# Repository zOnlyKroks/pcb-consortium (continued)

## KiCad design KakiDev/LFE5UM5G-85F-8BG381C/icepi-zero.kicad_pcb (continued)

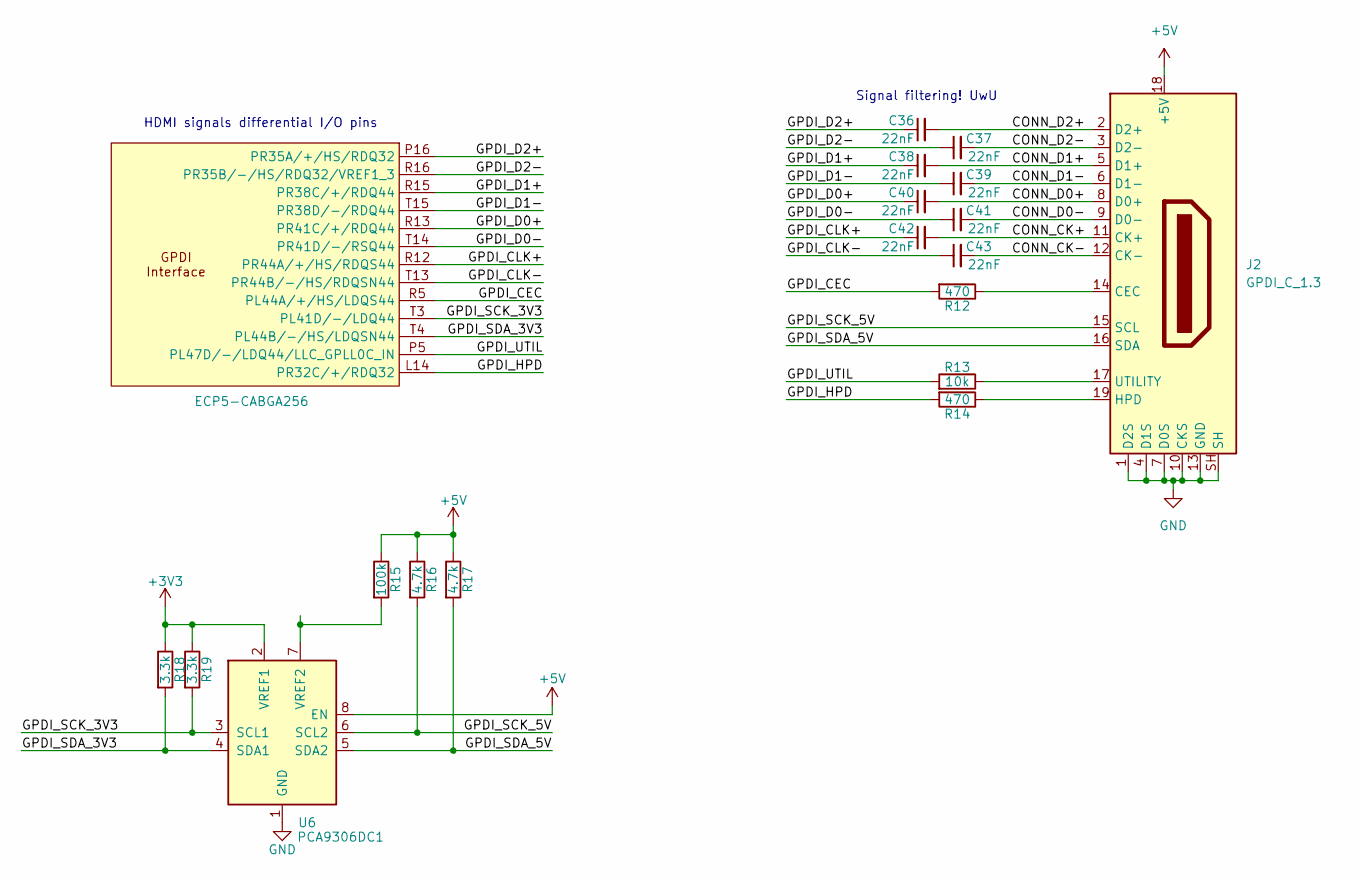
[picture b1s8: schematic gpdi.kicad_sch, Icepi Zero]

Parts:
C36, C37, C38, C39, C40, C41, C42, C43: 22nF; C_0603_1608Metric; Manufactuer Part Number 0402B223K500NT; LCSC Part # C1532
J2: GPDI_C_1.3; XKB Connection A71-05H4-111N1; Manufactuer Part Number A71-05H4-111N1; LCSC Part # C2682170
R12, R14: 470; R_0603_1608Metric; Manufactuer Part Number 0402WGF4700TCE; LCSC Part # C25117
R13: 10k; R_0603_1608Metric; Manufactuer Part Number 0402WGF1002TCE; LCSC Part # C25744
R15: 100k; R_0603_1608Metric; Manufactuer Part Number 0402WGF1003TCE; LCSC Part # C25741
R16, R17: 4.7k; R_0603_1608Metric; Manufactuer Part Number 0402WGF4701TCE; LCSC Part # C25900
R18, R19: 3.3k; R_0603_1608Metric; Manufactuer Part Number 0402WGF3301TCE; LCSC Part # C25890
U1: ECP5-CABGA256; BGA-256_14.0x14.0mm_Layout16x16_P0.8mm_Ball0.45mm_Pad0.32mm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; Manufactuer Part Number LFE5U-25F-6BG256C; LCSC Part # C1521614
U6: PCA9306DC1; VSSOP-8_2.3x2mm_P0.5mm; Manufactuer Part Number PCA9306DC1; LCSC Part # C129510

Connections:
+3V3: R18.1, R19.1, U6.2 (VREF1); also elsewhere on the board
+5V: J2.18 (+5V), R15.1, R16.1, R17.1, U6.8 (EN); also elsewhere on the board
/GPDI/CONN_CK+: C42.2, J2.11 (CK+)
/GPDI/CONN_CK-: C43.2, J2.12 (CK-)
/GPDI/CONN_D0+: C40.2, J2.8 (D0+)
/GPDI/CONN_D0-: C41.2, J2.9 (D0-)
/GPDI/CONN_D1+: C38.2, J2.5 (D1+)
/GPDI/CONN_D1-: C39.2, J2.6 (D1-)
/GPDI/CONN_D2+: C36.2, J2.2 (D2+)
/GPDI/CONN_D2-: C37.2, J2.3 (D2-)
/GPDI/GPDI_CEC: R12.2, U1.R5 (PL44A/+/HS/LDQS44)
/GPDI/GPDI_CLK+: C42.1, U1.R12 (PR44A/+/HS/RDQS44)
/GPDI/GPDI_CLK-: C43.1, U1.T13 (PR44B/-/HS/RDQSN44)
/GPDI/GPDI_D0+: C40.1, U1.R13 (PR41C/+/RDQ44)
/GPDI/GPDI_D0-: C41.1, U1.T14 (PR41D/-/RSQ44)
/GPDI/GPDI_D1+: C38.1, U1.R15 (PR38C/+/RDQ44)
/GPDI/GPDI_D1-: C39.1, U1.T15 (PR38D/-/RDQ44)
/GPDI/GPDI_D2+: C36.1, U1.P16 (PR35A/+/HS/RDQ32)
/GPDI/GPDI_D2-: C37.1, U1.R16 (PR35B/-/HS/RDQ32/VREF1_3)
/GPDI/GPDI_HPD: R14.2, U1.L14 (PR32C/+/RDQ32)
/GPDI/GPDI_SCK_3V3: R19.2, U1.T3 (PL41D/-/LDQ44), U6.3 (SCL1)
/GPDI/GPDI_SCK_5V: J2.15 (SCL), R16.2, U6.6 (SCL2)
/GPDI/GPDI_SDA_3V3: R18.2, U1.T4 (PL44B/-/HS/LDQSN44), U6.4 (SDA1)
/GPDI/GPDI_SDA_5V: J2.16 (SDA), R17.2, U6.5 (SDA2)
/GPDI/GPDI_UTIL: R13.2, U1.P5 (PL47D/-/LDQ44/LLC_GPLL0C_IN)
GND: J2.1 (D2S), J2.4 (D1S), J2.7 (D0S), J2.10 (CKS), J2.13 (GND), J2.SH, U6.1 (GND); also elsewhere on the board
unnamed: J2.14 (CEC), R12.1
unnamed: J2.19 (HPD), R14.1
unnamed: J2.17 (UTILITY), R13.1
unnamed: R15.2, U6.7 (VREF2)

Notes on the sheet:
HDMI signals differential I/O pins
Signal filtering! UwU

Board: 4 copper layers, 134 parts (0 on the bottom side), 246 nets, no tracks yet.

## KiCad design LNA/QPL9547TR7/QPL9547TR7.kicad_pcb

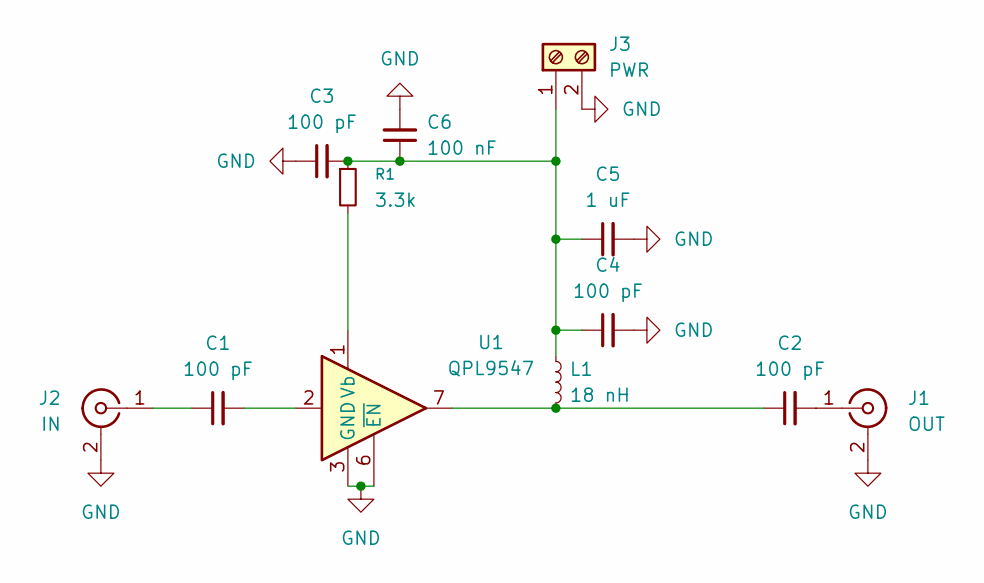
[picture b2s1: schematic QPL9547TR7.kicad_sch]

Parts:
C1, C2, C3, C4: 100 pF; C_0603_1608Metric
C5: 1 uF; C_0603_1608Metric
C6: 100 nF; C_0603_1608Metric
J1: OUT; SMA_BAT_Wireless_BWSMA-KWE-Z001
J2: IN; SMA_BAT_Wireless_BWSMA-KWE-Z001
J3: PWR; WJ500V-5.08-2P
L1: 18 nH; L_0805_2012Metric
R1: 3.3k; R_0603_1608Metric
U1: QPL9547; DFN-8-1EP_2x2mm_P0.5mm_EP0.8x1.6mm

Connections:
GND: C3.1, C4.2, C5.2, C6.2, J1.2 (Ext), J2.2 (Ext), J3.2, U1.3 (GND), U1.4 (GND), U1.5 (GND), U1.6 (~EN), U1.8 (GND), U1.9 (GND)
unnamed: C1.2, U1.2
unnamed: C2.1, L1.2, U1.7
unnamed: C2.2, J1.1 (In)
unnamed: C1.1, J2.1 (In)
unnamed: C3.2, C4.1, C5.1, C6.1, J3.1, L1.1, R1.1
unnamed: R1.2, U1.1 (Vb)

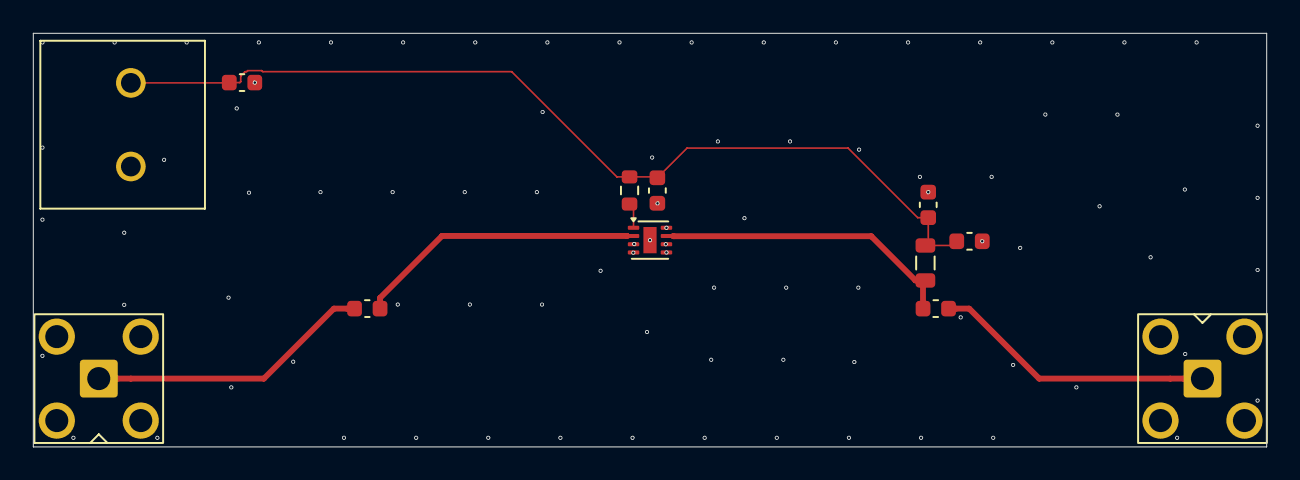
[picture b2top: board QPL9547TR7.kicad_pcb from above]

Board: 4 copper layers, 74.9 x 25.1 mm, 12 parts (0 on the bottom side), 7 nets.

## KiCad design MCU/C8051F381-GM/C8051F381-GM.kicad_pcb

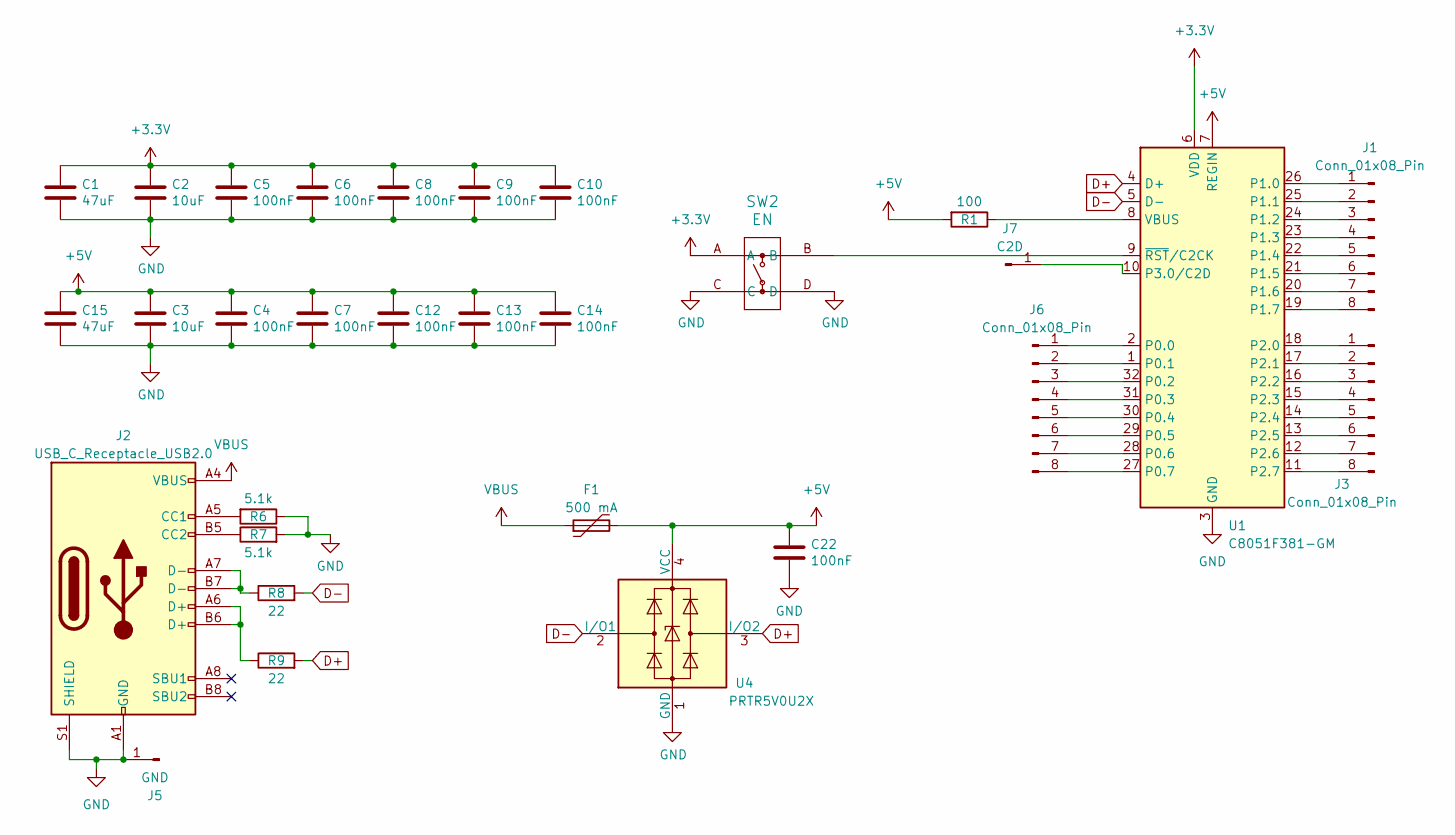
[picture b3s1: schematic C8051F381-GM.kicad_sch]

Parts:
C1, C15: 47uF; C_1206_3216Metric; LCSC C96123
C2, C3: 10uF; C_0603_1608Metric; LCSC C19702
C4, C5, C6, C7, C8, C9, C10, C12, C13, C14, C22: 100nF; C_0603_1608Metric; LCSC C14663
F1: 500 mA; Fuse_1206_3216Metric; LCSC C135341
J1, J3, J6: Conn_01x08_Pin; PinHeader_1x08_P2.54mm_Vertical
J2: USB_C_Receptacle_USB2.0; USB_C_Receptacle_HRO_TYPE-C-31-M-12; JlcRotOffset 180
J5: GND; PinHeader_1x01_P2.54mm_Vertical; LCSC Part # C492400
J7: C2D; PinHeader_1x01_P2.54mm_Vertical
R1: 100; R_0603_1608Metric; LCSC Part # C23186
R6, R7: 5.1k; R_0603_1608Metric; LCSC Part # C23186
R8, R9: 22; R_0603_1608Metric; LCSC Part # C23345
SW2: EN; KH-6X6X5H-STM_SKE; LCSC Part # C2837531
U1: C8051F381-GM; QFN-32-1EP_5x5mm_P0.5mm_EP3.3x3.3mm; LCSC Part # C1522096
U4: PRTR5V0U2X; SOT-143; LCSC C2827688

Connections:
+3.3V: C1.1, C2.1, C5.1, C6.1, C8.1, C9.1, C10.1, SW2.A, U1.6 (VDD)
+5V: C3.1, C4.1, C7.1, C12.1, C13.1, C14.1, C15.1, C22.1, F1.2, R1.2, U1.7 (REGIN), U4.4 (VCC)
D+: R9.2, U1.4 (D+), U4.3 (I/O2)
D-: R8.2, U1.5 (D-), U4.2 (I/O1)
GND: C1.2, C2.2, C3.2, C4.2, C5.2, C6.2, C7.2, C8.2, C9.2, C10.2, C12.2, C13.2, C14.2, C15.2, C22.2, J2.A1 (GND), J2.A12 (GND), J2.B1 (GND), J2.B12 (GND), J2.S1 (SHIELD), J5.1, R6.1, R7.2, SW2.C, SW2.D, U1.3 (GND), U1.33 (GND), U4.1 (GND)
unnamed: J1.1, U1.26 (P1.0)
unnamed: J1.2, U1.25 (P1.1)
unnamed: J1.3, U1.24 (P1.2)
unnamed: J1.4, U1.23 (P1.3)
unnamed: J1.5, U1.22 (P1.4)
unnamed: J1.6, U1.21 (P1.5)
unnamed: J1.7, U1.20 (P1.6)
unnamed: J1.8, U1.19 (P1.7)
unnamed: J2.A5 (CC1), R6.2
unnamed: J2.B5 (CC2), R7.1
unnamed: J2.A6 (D+), J2.B6 (D+), R9.1
unnamed: J2.A7 (D-), J2.B7 (D-), R8.1
unnamed: J3.1, U1.18 (P2.0)
unnamed: J3.2, U1.17 (P2.1)
unnamed: J3.3, U1.16 (P2.2)
unnamed: J3.4, U1.15 (P2.3)
unnamed: J3.5, U1.14 (P2.4)
unnamed: J3.6, U1.13 (P2.5)
unnamed: J3.7, U1.12 (P2.6)
unnamed: J3.8, U1.11 (P2.7)
unnamed: J6.1, U1.2 (P0.0)
unnamed: J6.2, U1.1 (P0.1)
unnamed: J6.3, U1.32 (P0.2)
unnamed: J6.4, U1.31 (P0.3)
unnamed: J6.5, U1.30 (P0.4)
unnamed: J6.6, U1.29 (P0.5)
unnamed: J6.7, U1.28 (P0.6)
unnamed: J6.8, U1.27 (P0.7)
unnamed: J7.1, U1.10 (P3.0/C2D)
unnamed: R1.1, U1.8 (VBUS)
unnamed: SW2.B, U1.9 (~RST/C2CK)
VBUS: F1.1, J2.A4 (VBUS), J2.A9 (VBUS), J2.B4 (VBUS), J2.B9 (VBUS)

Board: 2 copper layers, 30 parts (0 on the bottom side), 37 nets, no tracks yet.

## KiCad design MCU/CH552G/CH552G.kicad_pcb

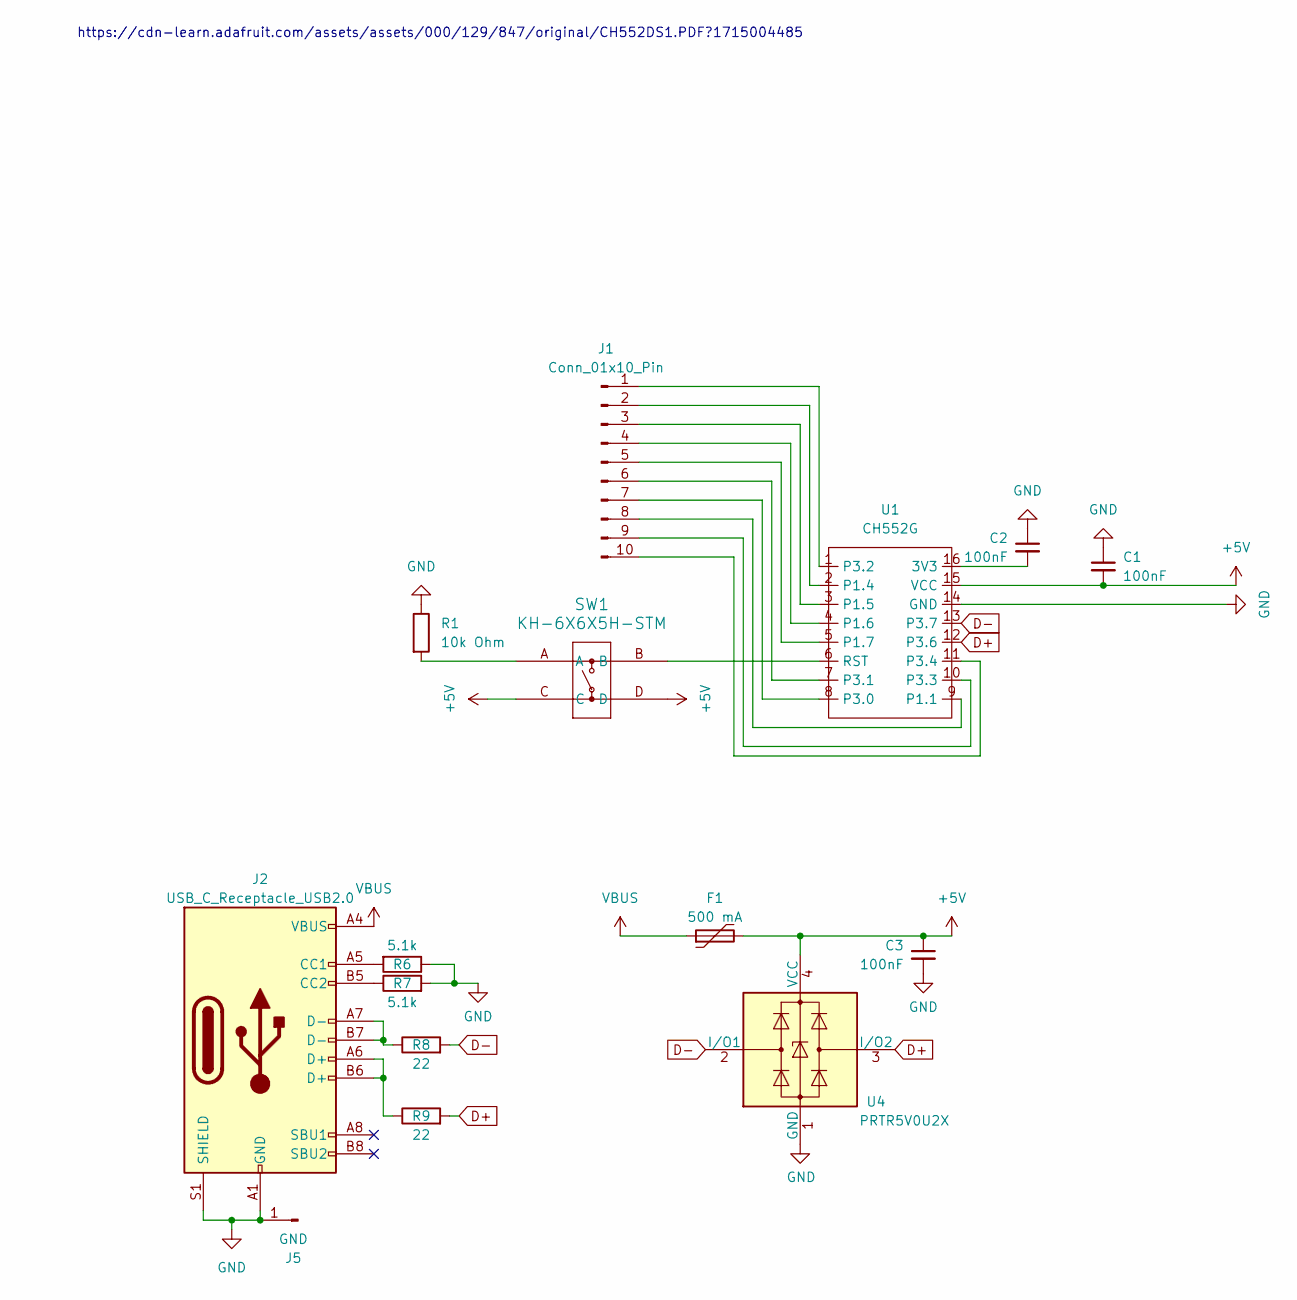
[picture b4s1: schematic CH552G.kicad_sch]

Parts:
C1, C2, C3: 100nF; C_0805_2012Metric; LCSC Part # C49678
F1: 500 mA; Fuse_1206_3216Metric; LCSC C135341
J1: Conn_01x10_Pin; PinHeader_1x10_P2.54mm_Vertical; LCSC Part # C492409
J2: USB_C_Receptacle_USB2.0; USB_C_Receptacle_HRO_TYPE-C-31-M-12; JlcRotOffset 180
J5: GND; PinHeader_1x01_P2.54mm_Vertical; LCSC Part # C492400
R1: 10k Ohm; R_0805_2012Metric; LCSC Part # C17414
R6, R7: 5.1k; R_0603_1608Metric; LCSC Part # C23186
R8, R9: 22; R_0603_1608Metric; LCSC Part # C23345
SW1: KH-6X6X5H-STM; KH-6X6X5H-STM_SKE; LCSC Part # C2837531
U1: CH552G; LCSC Part # C111292
U4: PRTR5V0U2X; SOT-143; LCSC C2827688

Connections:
+5V: C1.2, C3.1, F1.2, SW1.C, SW1.D, U1.15 (VCC), U4.4 (VCC)
D+: R9.2, U1.12 (P3.6), U4.3 (I/O2)
D-: R8.2, U1.13 (P3.7), U4.2 (I/O1)
GND: C1.1, C2.1, C3.2, J2.A1 (GND), J2.A12 (GND), J2.B1 (GND), J2.B12 (GND), J2.S1 (SHIELD), J5.1, R1.1, R6.1, R7.2, U1.14 (GND), U4.1 (GND)
unnamed: J1.1, U1.1 (P3.2)
unnamed: J1.2, U1.2 (P1.4)
unnamed: J1.3, U1.3 (P1.5)
unnamed: J1.4, U1.4 (P1.6)
unnamed: J1.5, U1.5 (P1.7)
unnamed: J1.6, U1.7 (P3.1)
unnamed: J1.7, U1.8 (P3.0)
unnamed: J1.8, U1.9 (P1.1)
unnamed: J1.9, U1.10 (P3.3)
unnamed: J1.10, U1.11 (P3.4)
unnamed: J2.A5 (CC1), R6.2
unnamed: J2.B5 (CC2), R7.1
unnamed: J2.A6 (D+), J2.B6 (D+), R9.1
unnamed: J2.A7 (D-), J2.B7 (D-), R8.1
unnamed: R1.2, SW1.A
unnamed: C2.2, U1.16 (3V3)
unnamed: SW1.B, U1.6 (RST)
VBUS: F1.1, J2.A4 (VBUS), J2.A9 (VBUS), J2.B4 (VBUS), J2.B9 (VBUS)

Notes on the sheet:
https://cdn-learn.adafruit.com/assets/assets/000/129/847/original/CH552DS1.PDF?1715004485

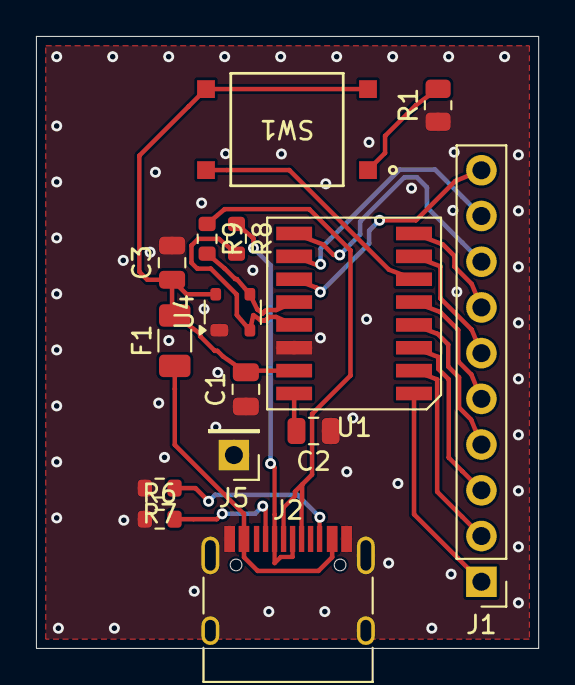
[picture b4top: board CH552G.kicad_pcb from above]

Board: 2 copper layers, 27.9 x 34.0 mm, 15 parts (0 on the bottom side), 22 nets.

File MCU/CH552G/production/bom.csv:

Designator,Footprint,Quantity,Value,LCSC Part #
"C1, C2, C3",0805,3,100nF,C49678
F1,1206,1,500 mA,C135341
J1,PinHeader_1x10_P2.54mm_Vertical,1,Conn_01x10_Pin,C492409
J2,USB_C_Receptacle_HRO_TYPE-C-31-M-12,1,USB_C_Receptacle_USB2.0,C165948
J5,PinHeader_1x01_P2.54mm_Vertical,1,GND,C492400
R1,0805,1,10k Ohm,C17414
"R6, R7",0603,2,5.1k,C23186
"R8, R9",0603,2,22,C23345
SW1,KH-6X6X5H-STM_SKE,1,KH-6X6X5H-STM,C2837531
U1,CH552G,1,CH552G,C111292
U4,SOT-143,1,PRTR5V0U2X,C2827688

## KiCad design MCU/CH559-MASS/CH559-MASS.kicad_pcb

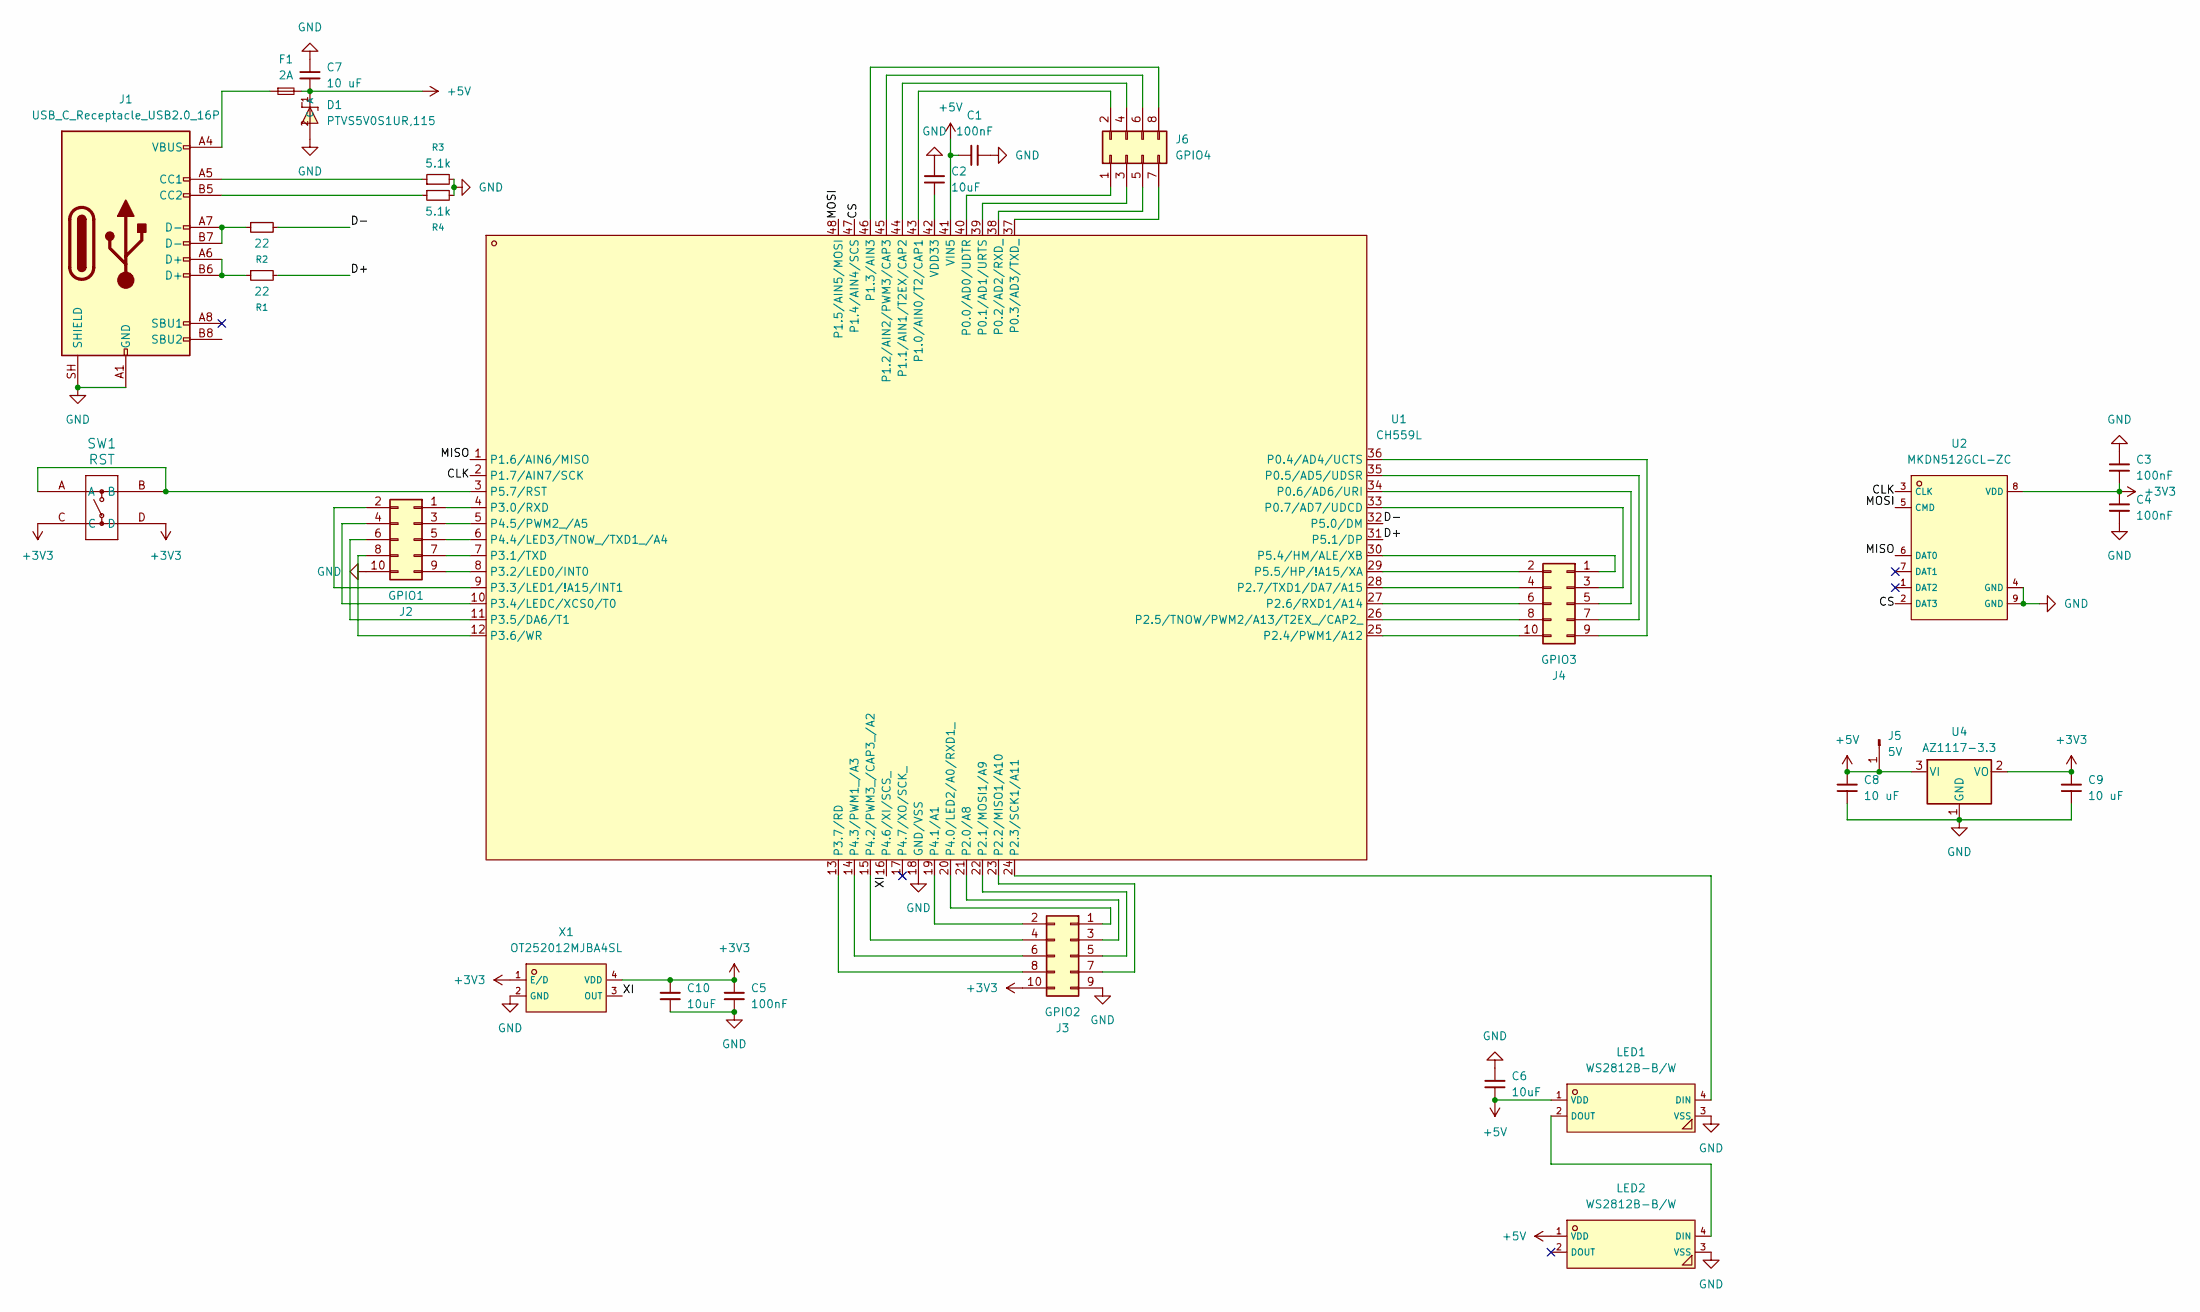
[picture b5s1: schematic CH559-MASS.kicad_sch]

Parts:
C1, C3, C4, C5: 100nF; C_0603_1608Metric
C2, C6: 10uF; C_0603_1608Metric
C7, C8, C9: 10 uF; C_0805_2012Metric
C10: 10uF; C_0805_2012Metric
D1: PTVS5V0S1UR,115; C478011_SOD-123_L2_8-W1_8-LS3_7-RD; LCSC C478011
F1: 2A; Fuse_0805_2012Metric
J1: USB_C_Receptacle_USB2.0_16P; USB_C_Receptacle_HRO_TYPE-C-31-M-12
J2: GPIO1; PinHeader_2x05_P2.54mm_Vertical
J3: GPIO2; PinHeader_2x05_P2.54mm_Vertical
J4: GPIO3; PinHeader_2x05_P2.54mm_Vertical
J5: 5V; PinHeader_1x01_P2.54mm_Vertical
J6: GPIO4; PinHeader_2x04_P2.54mm_Vertical
LED1, LED2: WS2812B-B/W; C2761795_LED-SMD_4P-L5_0-W5_0-TL_WS2812B-B; LCSC C2761795
R1, R2: 22; R_0603_1608Metric
R3, R4: 5.1k; R_0603_1608Metric
SW1: RST; KH-6X6X5H-STM_SKE
U1: CH559L; MPN CH559L; LCSC Part C150548
U2: MKDN512GCL-ZC; C52753986_LGA-16_L12_5-W9_0-P1_27-TL-EP; LCSC C52753986
U4: AZ1117-3.3; SOT-89-3
X1: OT252012MJBA4SL; C669073_OSC-SMD_4P-L2_5-W2_0-BL; LCSC C669073

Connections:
+3V3: C3.1, C4.2, C5.2, C9.1, C10.1, J3.10, SW1.C, SW1.D, U2.8 (VDD), U4.2 (VO), X1.1 (E/D), X1.4 (VDD)
+5V: C1.1, C6.1, C7.2, C8.1, D1.1 (C), F1.2, J5.1 (Pin_1_1), LED1.1 (VDD), LED2.1 (VDD), U1.41 (VIN5), U4.3 (VI)
/CLK: U1.2 (P1.7/AIN7/SCK), U2.3 (CLK)
/CS: U1.47 (P1.4/AIN4/SCS), U2.2 (DAT3)
/D+: R1.2, U1.31 (P5.1/DP)
/D-: R2.2, U1.32 (P5.0/DM)
/MISO: U1.1 (P1.6/AIN6/MISO), U2.6 (DAT0)
/MOSI: U1.48 (P1.5/AIN5/MOSI), U2.5 (CMD)
/XI: U1.16 (P4.6/XI/SCS_), X1.3 (OUT)
GND: C1.2, C2.2, C3.2, C4.1, C5.1, C6.2, C7.1, C8.2, C9.2, C10.2, D1.2 (A), J1.A1 (GND), J1.A12 (GND), J1.B1 (GND), J1.B12 (GND), J1.SH (SHIELD), J2.10, J3.9, LED1.3 (VSS), LED2.3 (VSS), R3.2, R4.2, U1.18 (GND/VSS), U2.4 (GND), U2.9 (GND), U4.1 (GND), X1.2 (GND)
unnamed: F1.1, J1.A4 (VBUS), J1.A9 (VBUS), J1.B4 (VBUS), J1.B9 (VBUS)
unnamed: J1.A5 (CC1), R3.1
unnamed: J1.B5 (CC2), R4.1
unnamed: J1.A6 (D+), J1.B6 (D+), R1.1
unnamed: J1.A7 (D-), J1.B7 (D-), R2.1
unnamed: J2.1, U1.4 (P3.0/RXD)
unnamed: J2.2, U1.9 (P3.3/LED1/!A15/INT1)
unnamed: J2.3, U1.5 (P4.5/PWM2_/A5)
unnamed: J2.4, U1.10 (P3.4/LEDC/XCS0/T0)
unnamed: J2.5, U1.6 (P4.4/LED3/TNOW_/TXD1_/A4)
unnamed: J2.6, U1.11 (P3.5/DA6/T1)
unnamed: J2.7, U1.7 (P3.1/TXD)
unnamed: J2.8, U1.12 (P3.6/WR)
unnamed: J2.9, U1.8 (P3.2/LED0/INT0)
unnamed: J3.1, U1.20 (P4.0/LED2/A0/RXD1_)
unnamed: J3.2, U1.19 (P4.1/A1)
unnamed: J3.3, U1.21 (P2.0/A8)
unnamed: J3.4, U1.15 (P4.2/PWM3_/CAP3_/A2)
unnamed: J3.5, U1.22 (P2.1/MOSI1/A9)
unnamed: J3.6, U1.14 (P4.3/PWM1_/A3)
unnamed: J3.7, U1.23 (P2.2/MISO1/A10)
unnamed: J3.8, U1.13 (P3.7/RD)
unnamed: J4.1, U1.30 (P5.4/HM/ALE/XB)
unnamed: J4.2, U1.29 (P5.5/HP/!A15/XA)
unnamed: J4.3, U1.33 (P0.7/AD7/UDCD)
unnamed: J4.4, U1.28 (P2.7/TXD1/DA7/A15)
unnamed: J4.5, U1.34 (P0.6/AD6/URI)
unnamed: J4.6, U1.27 (P2.6/RXD1/A14)
unnamed: J4.7, U1.35 (P0.5/AD5/UDSR)
unnamed: J4.8, U1.26 (P2.5/TNOW/PWM2/A13/T2EX_/CAP2_)
unnamed: J4.9, U1.36 (P0.4/AD4/UCTS)
unnamed: J4.10, U1.25 (P2.4/PWM1/A12)
unnamed: J6.1, U1.40 (P0.0/AD0/UDTR)
unnamed: J6.2, U1.43 (P1.0/AIN0/T2/CAP1)
unnamed: J6.3, U1.39 (P0.1/AD1/URTS)
unnamed: J6.4, U1.44 (P1.1/AIN1/T2EX/CAP2)
unnamed: J6.5, U1.38 (P0.2/AD2/RXD_)
unnamed: J6.6, U1.45 (P1.2/AIN2/PWM3/CAP3)
unnamed: J6.7, U1.37 (P0.3/AD3/TXD_)
unnamed: J6.8, U1.46 (P1.3/AIN3)
unnamed: LED1.4 (DIN), U1.24 (P2.3/SCK1/A11)
unnamed: LED1.2 (DOUT), LED2.4 (DIN)
unnamed: SW1.A, SW1.B, U1.3 (P5.7/RST)
unnamed: C2.1, U1.42 (VDD33)

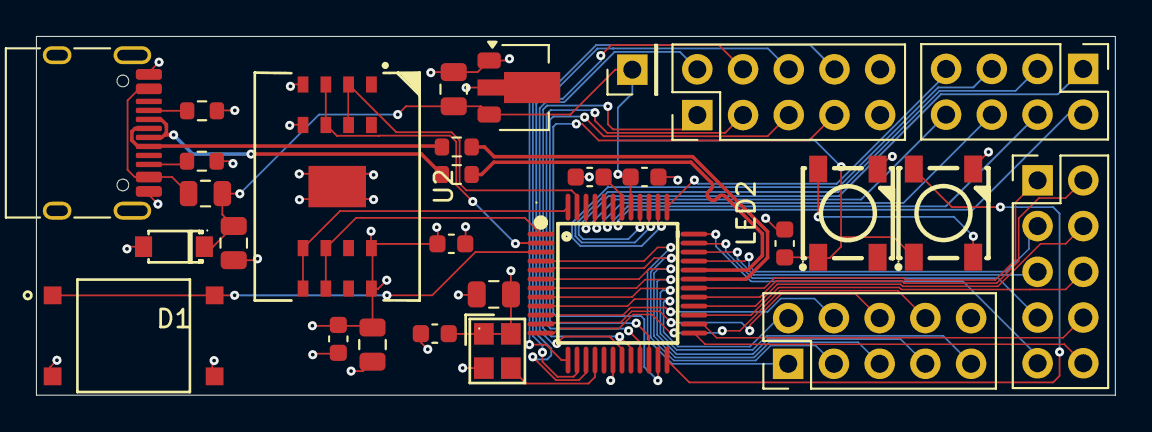
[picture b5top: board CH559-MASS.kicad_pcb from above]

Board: 4 copper layers, 59.9 x 19.9 mm, 29 parts (0 on the bottom side), 54 nets.

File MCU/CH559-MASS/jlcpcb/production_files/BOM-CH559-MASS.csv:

Comment,Designator,Footprint,LCSC,Quantity
10 uF,"C7,C8,C9",C_0805_2012Metric,C15850,3
100nF,"C1,C3,C4,C5",C_0603_1608Metric,C14663,4
10uF,C10,C_0805_2012Metric,C15850,1
10uF,C2,C_0603_1608Metric,C19702,1
10uF,C6,C_0603_1608Metric,C96446,1
22,"R1,R2",R_0603_1608Metric,C23345,2
2A,F1,Fuse_0805_2012Metric,C22363531,1
5.1k,"R3,R4",R_0603_1608Metric,C23186,2
5V,J5,PinHeader_1x01_P2.54mm_Vertical,C27985186,1
AZ1117-3.3,U4,SOT-89-3,C108493,1
CH559L,U1,CH559L,C150548,1
GPIO1,J2,PinHeader_2x05_P2.54mm_Vertical,C42431818,1
GPIO2,J3,PinHeader_2x05_P2.54mm_Vertical,C42431818,1
GPIO3,J4,PinHeader_2x05_P2.54mm_Vertical,C42431818,1
GPIO4,J6,PinHeader_2x04_P2.54mm_Vertical,C32713277,1
MKDN128GCL-AB,U3,MKDN128GCL-AB,C54820826,1
OT252012MJBA4SL,X1,C669073_OSC-SMD_4P-L2_5-W2_0-BL,C669073,1
"PTVS5V0S1UR,115",D1,C478011_SOD-123_L2_8-W1_8-LS3_7-RD,C478011,1
RST,SW1,KH-6X6X5H-STM_SKE,C2837531,1
USB_C_Receptacle_USB2.0_16P,J1,USB_C_Receptacle_HRO_TYPE-C-31-M-12,C165948,1
WS2812B-B/W,"LED1,LED2",C2761795_LED-SMD_4P-L5_0-W5_0-TL_WS2812B-B,C2761795,2

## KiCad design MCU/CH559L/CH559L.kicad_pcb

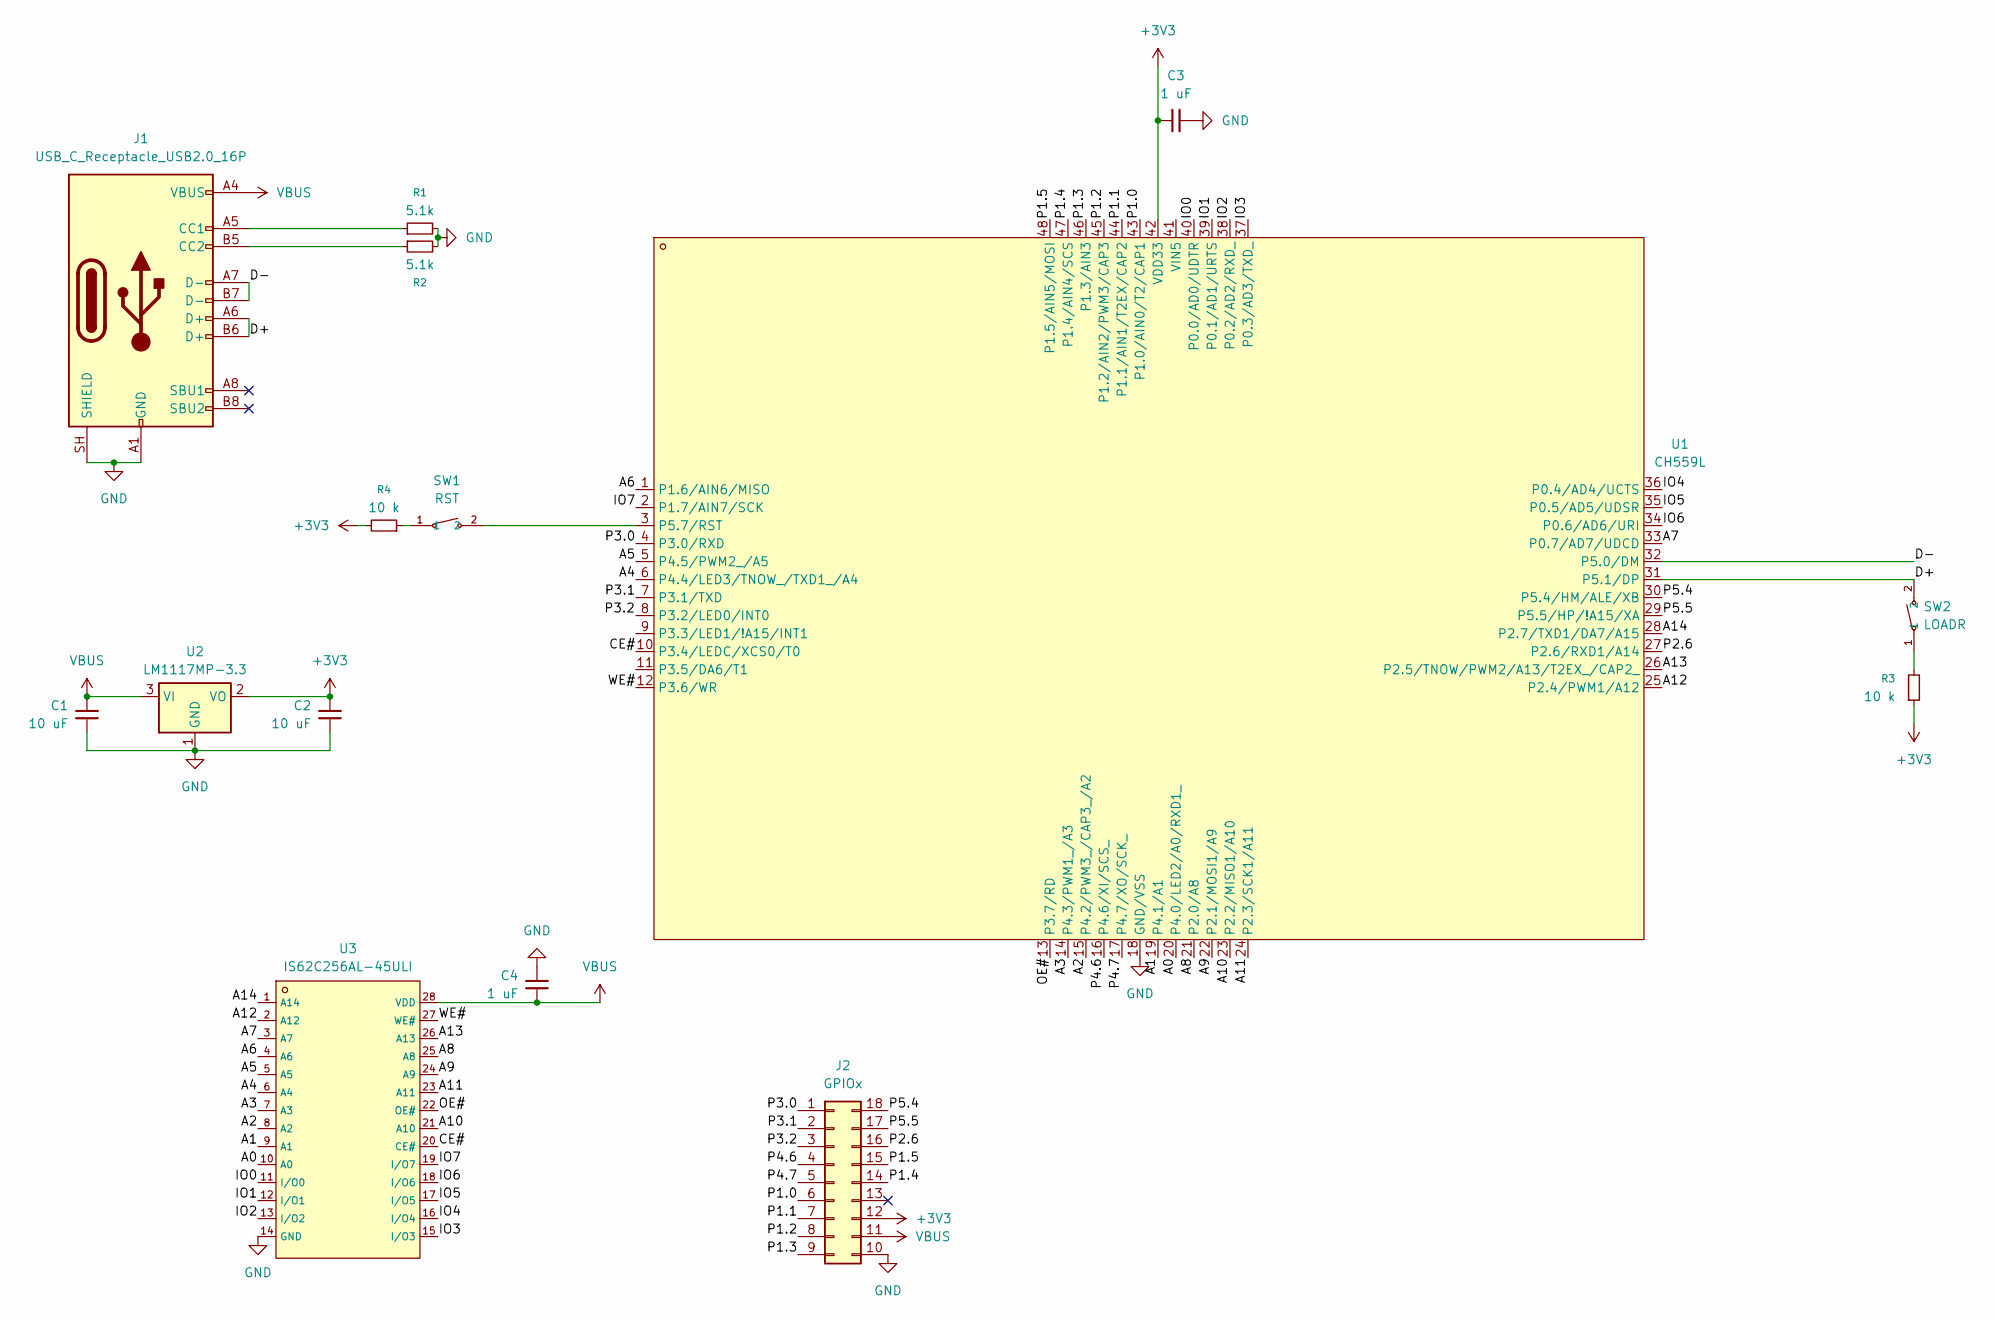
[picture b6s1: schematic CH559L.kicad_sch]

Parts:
C1, C2: 10 uF; C_0805_2012Metric
C3, C4: 1 uF; C_0805_2012Metric
J1: USB_C_Receptacle_USB2.0_16P; USB_C_Receptacle_HRO_TYPE-C-31-M-12
J2: GPIOx; PinHeader_2x09_P2.54mm_Vertical
R1, R2: 5.1k; R_0805_2012Metric
R3, R4: 10 k; R_0805_2012Metric
SW1: RST; C53447012_SW-SMD_L3_9-W3_0-LS5_0; LCSC C53447012
SW2: LOADR; C53447012_SW-SMD_L3_9-W3_0-LS5_0; LCSC C53447012
U1: CH559L; MPN CH559L; LCSC Part C150548
U2: LM1117MP-3.3; SOT-223-3_TabPin2
U3: IS62C256AL-45ULI; C14323_SOIC-28_L17_9-W8_4-P1_27-LS12_7-BL; LCSC C14323

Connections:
+3V3: C2.1, C3.1, J2.12, R3.1, R4.2, U1.42 (VDD33), U2.2 (VO)
/A0: U1.20 (P4.0/LED2/A0/RXD1_), U3.10 (A0)
/A1: U1.19 (P4.1/A1), U3.9 (A1)
/A2: U1.15 (P4.2/PWM3_/CAP3_/A2), U3.8 (A2)
/A3: U1.14 (P4.3/PWM1_/A3), U3.7 (A3)
/A4: U1.6 (P4.4/LED3/TNOW_/TXD1_/A4), U3.6 (A4)
/A5: U1.5 (P4.5/PWM2_/A5), U3.5 (A5)
/A6: U1.1 (P1.6/AIN6/MISO), U3.4 (A6)
/A7: U1.33 (P0.7/AD7/UDCD), U3.3 (A7)
/A8: U1.21 (P2.0/A8), U3.25 (A8)
/A9: U1.22 (P2.1/MOSI1/A9), U3.24 (A9)
/A10: U1.23 (P2.2/MISO1/A10), U3.21 (A10)
/A11: U1.24 (P2.3/SCK1/A11), U3.23 (A11)
/A12: U1.25 (P2.4/PWM1/A12), U3.2 (A12)
/A13: U1.26 (P2.5/TNOW/PWM2/A13/T2EX_/CAP2_), U3.26 (A13)
/A14: U1.28 (P2.7/TXD1/DA7/A15), U3.1 (A14)
/CE#: U1.10 (P3.4/LEDC/XCS0/T0), U3.20 (CE#)
/D+: J1.A6 (D+), J1.B6 (D+), SW2.2, U1.31 (P5.1/DP)
/D-: J1.A7 (D-), J1.B7 (D-), U1.32 (P5.0/DM)
/IO0: U1.40 (P0.0/AD0/UDTR), U3.11 (I/O0)
/IO1: U1.39 (P0.1/AD1/URTS), U3.12 (I/O1)
/IO2: U1.38 (P0.2/AD2/RXD_), U3.13 (I/O2)
/IO3: U1.37 (P0.3/AD3/TXD_), U3.15 (I/O3)
/IO4: U1.36 (P0.4/AD4/UCTS), U3.16 (I/O4)
/IO5: U1.35 (P0.5/AD5/UDSR), U3.17 (I/O5)
/IO6: U1.34 (P0.6/AD6/URI), U3.18 (I/O6)
/IO7: U1.2 (P1.7/AIN7/SCK), U3.19 (I/O7)
/OE#: U1.13 (P3.7/RD), U3.22 (OE#)
/P1.0: J2.6, U1.43 (P1.0/AIN0/T2/CAP1)
/P1.1: J2.7, U1.44 (P1.1/AIN1/T2EX/CAP2)
/P1.2: J2.8, U1.45 (P1.2/AIN2/PWM3/CAP3)
/P1.3: J2.9, U1.46 (P1.3/AIN3)
/P1.4: J2.14, U1.47 (P1.4/AIN4/SCS)
/P1.5: J2.15, U1.48 (P1.5/AIN5/MOSI)
/P2.6: J2.16, U1.27 (P2.6/RXD1/A14)
/P3.0: J2.1, U1.4 (P3.0/RXD)
/P3.1: U1.7 (P3.1/TXD)
/P3.2: J2.3
/P4.6: J2.4, U1.16 (P4.6/XI/SCS_)
/P4.7: J2.5, U1.17 (P4.7/XO/SCK_)
/P5.4: J2.18, U1.30 (P5.4/HM/ALE/XB)
/P5.5: J2.17, U1.29 (P5.5/HP/!A15/XA)
/WE#: U1.12 (P3.6/WR), U3.27 (WE#)
GND: C1.2, C2.2, C3.2, C4.2, J1.A1 (GND), J1.A12 (GND), J1.B1 (GND), J1.B12 (GND), J1.SH (SHIELD), J2.10, R1.2, R2.2, U1.18 (GND/VSS), U2.1 (GND), U3.14 (GND)
unnamed: J1.A5 (CC1), R1.1
unnamed: J1.B5 (CC2), R2.1
unnamed: R3.2, SW2.1
unnamed: R4.1, SW1.1
unnamed: SW1.2, U1.3 (P5.7/RST)
VBUS: C1.1, C4.1, J1.A4 (VBUS), J1.A9 (VBUS), J1.B4 (VBUS), J1.B9 (VBUS), J2.11, U2.3 (VI), U3.28 (VDD)

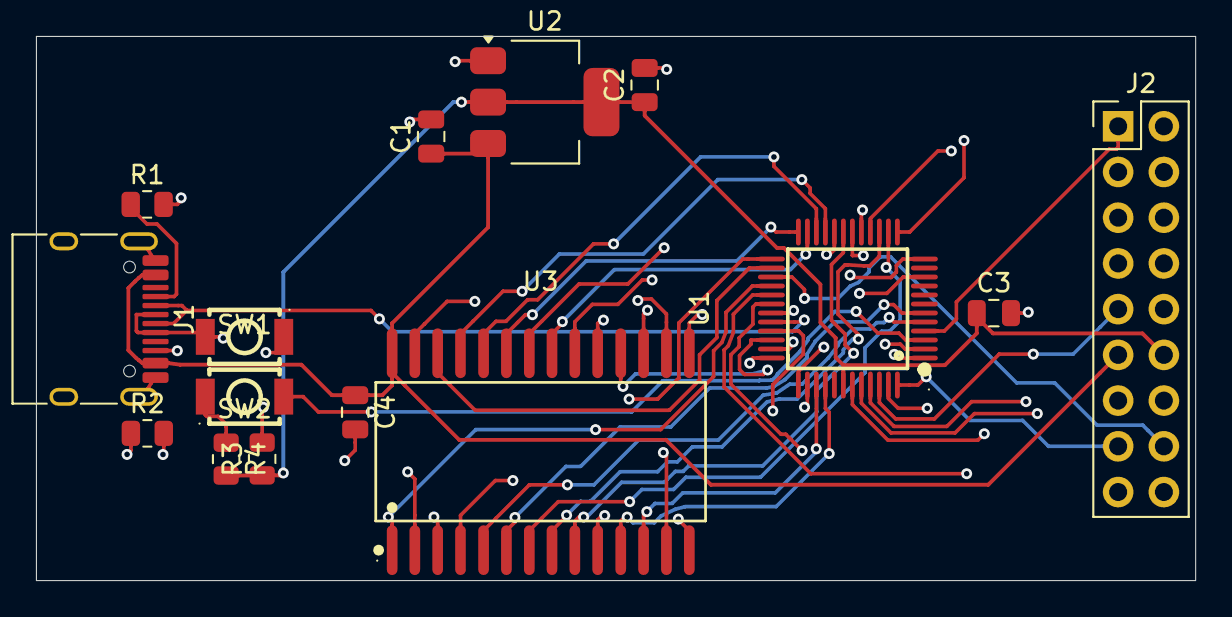
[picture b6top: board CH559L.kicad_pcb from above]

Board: 4 copper layers, 64.4 x 30.2 mm, 15 parts (0 on the bottom side), 48 nets.
